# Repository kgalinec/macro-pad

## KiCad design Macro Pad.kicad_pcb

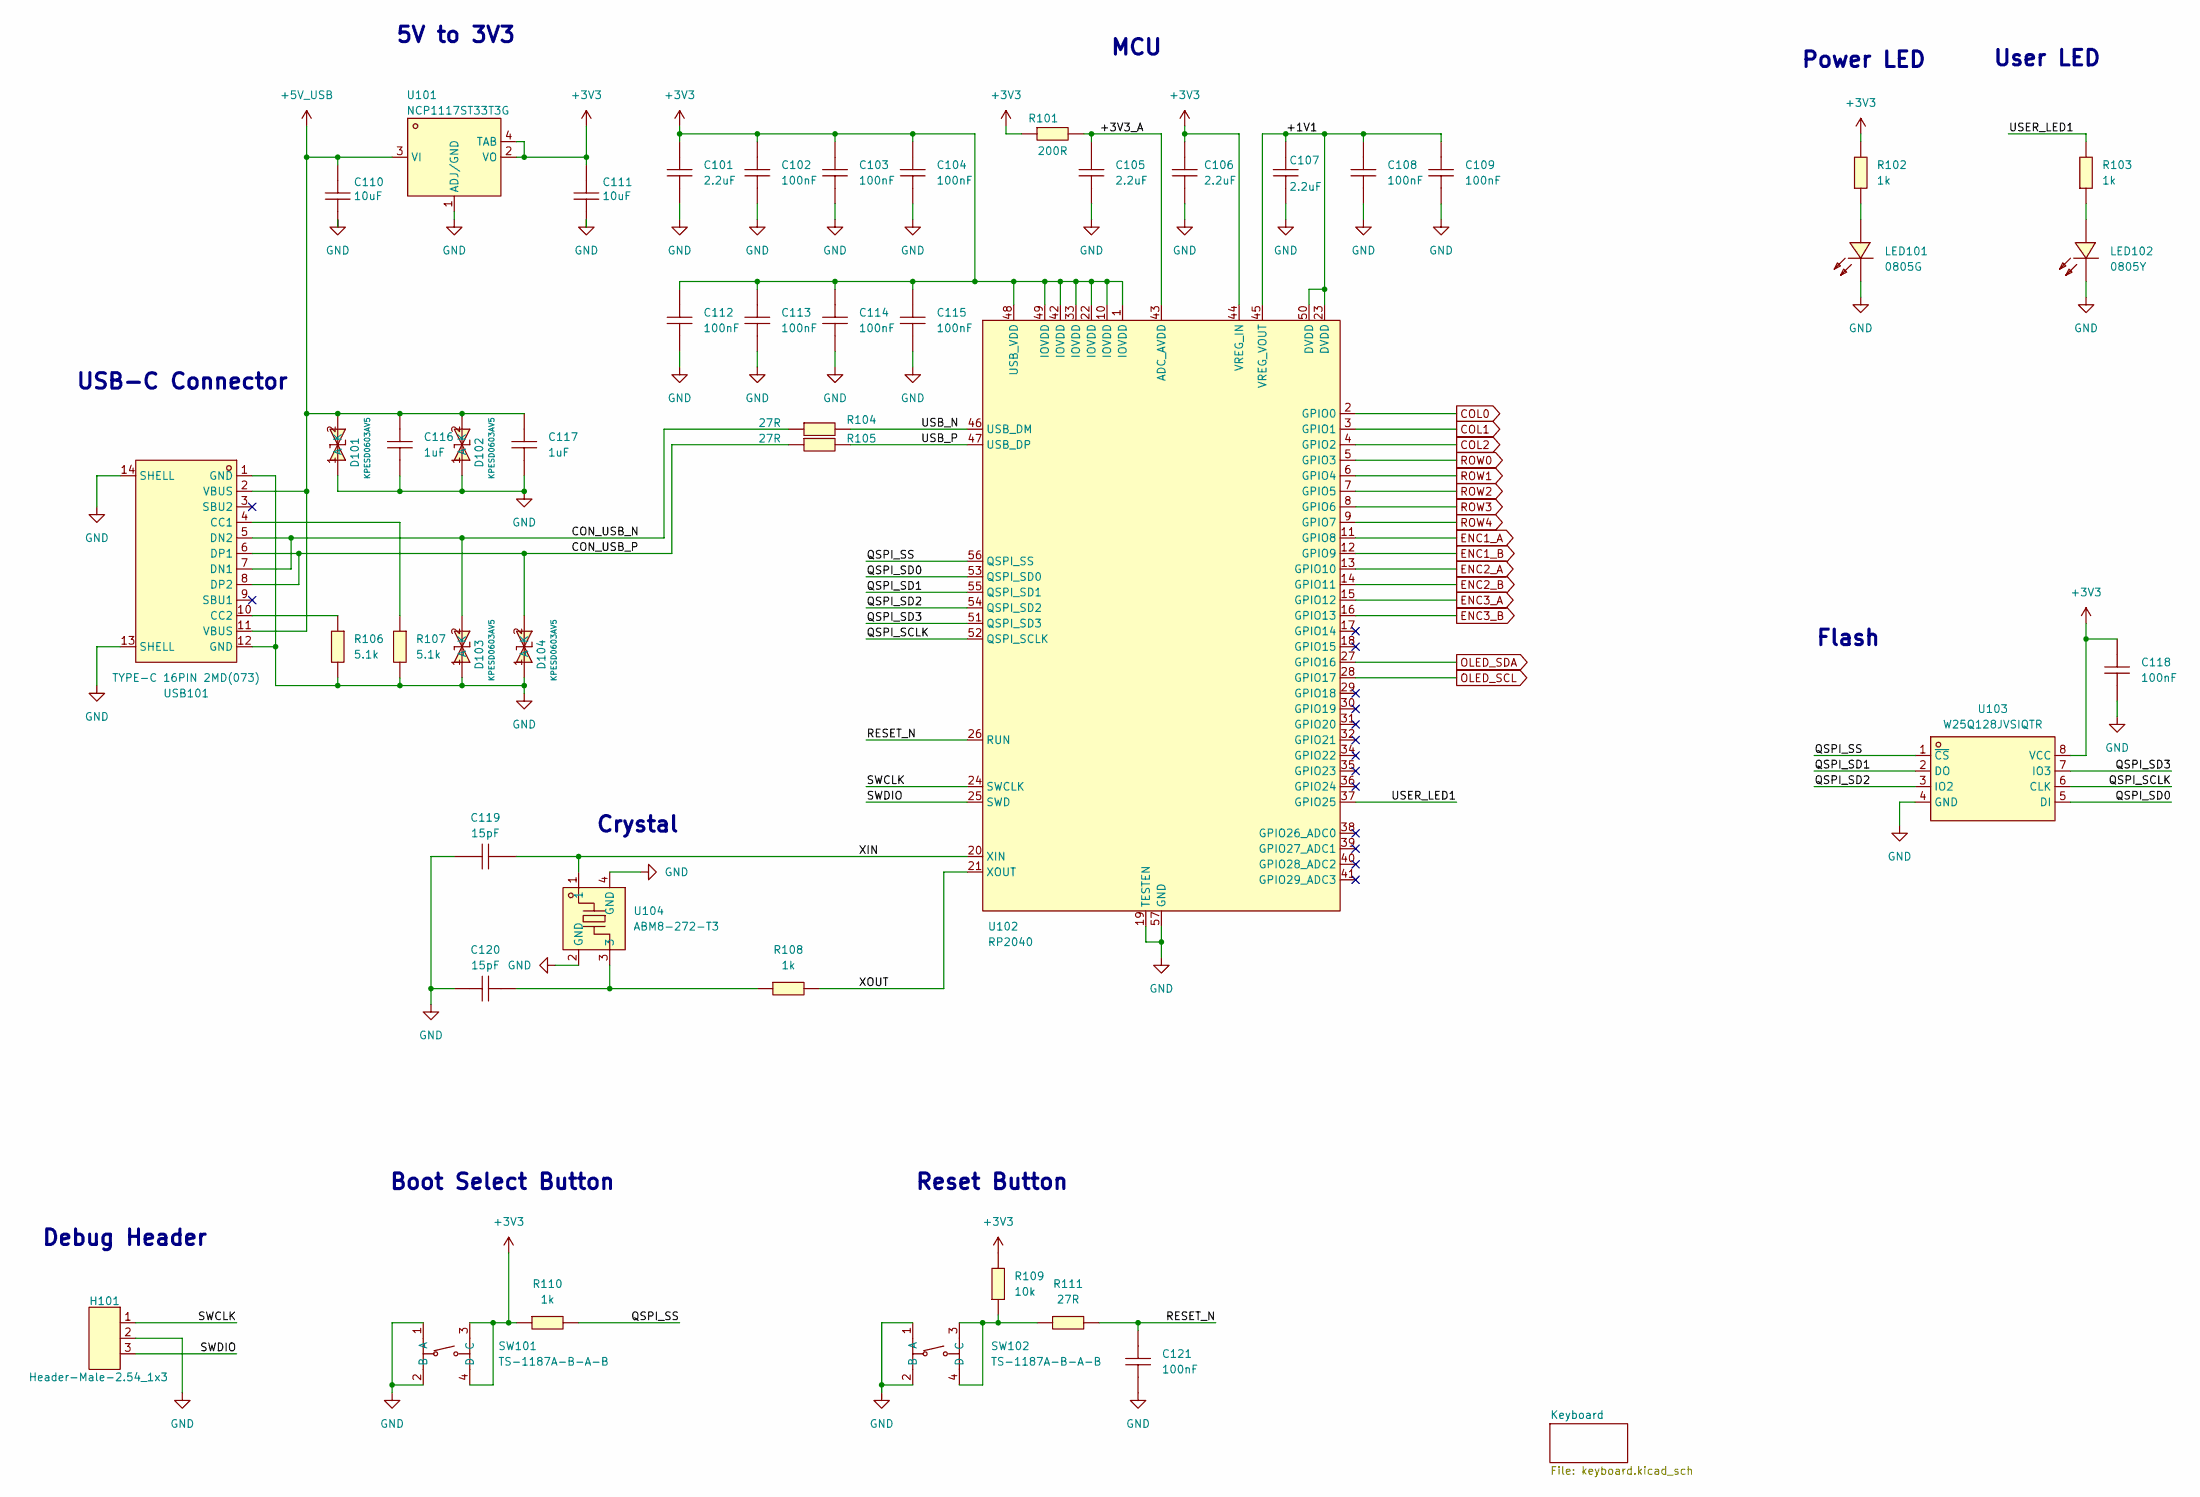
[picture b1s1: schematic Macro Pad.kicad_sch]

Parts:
C101, C105, C106, C107: 2.2uF; C0603; LCSC Part C23630
C102, C103, C104, C108, C109, C112, C113, C114, C115, C118, C121: 100nF; C0603; LCSC Part C1591
C110, C111: 10uF; C0603; LCSC Part C1691
C116, C117: 1uF; C0603; LCSC Part C15849
C119, C120: 15pF; C0603; LCSC Part C1644
D101, D102, D103, D104: KPESD0603AV5; D0603-BI-A; LCSC Part C2944167
H101: Header-Male-2.54_1x3; HDR-TH_3P-P2.54-V-M-1; LCSC Part C49257
LED101: 0805G; LED0805-R-RD; LCSC Part C2297
LED102: 0805Y; LED0805-R-RD; LCSC Part C2296
R101: 200R; R0603; LCSC Part C8218
R102, R103, R108, R110: 1k; R0603; LCSC Part C21190
R104, R105, R111: 27R; R0603; LCSC Part C25190
R106, R107: 5.1k; R0603; LCSC Part C23186
R109: 10k; R0603; LCSC Part C25804
SW101, SW102: TS-1187A-B-A-B; SW-SMD_4P-L5.1-W5.1-P3.70-LS6.5-TL_H1.5; LCSC Part C318884
U101: NCP1117ST33T3G; SOT-223-3_L6.5-W3.4-P2.30-LS7.0-BR; LCSC Part C26537
U102: RP2040; LQFN-56_L7.0-W7.0-P0.4-EP; LCSC Part C2040
U103: W25Q128JVSIQTR; SOIC-8_L5.3-W5.3-P1.27-LS8.0-BL; LCSC Part C97521
U104: ABM8-272-T3; CRYSTAL-SMD_4P-L3.2-W2.5-BL; LCSC Part C20625731
USB101: TYPE-C 16PIN 2MD(073); USB-C-SMD_TYPE-C-6PIN-2MD-073; LCSC Part C2765186

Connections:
+3V3: C101.2, C102.2, C103.2, C104.2, C106.2, C111.2, C112.2, C113.2, C114.2, C115.2, C118.2, R101.1, R102.2, R109.2, R110.1, SW101.3 (C), SW101.4 (D), U101.2 (VO), U101.4 (TAB), U102.1 (IOVDD), U102.10 (IOVDD), U102.22 (IOVDD), U102.33 (IOVDD), U102.42 (IOVDD), U102.44 (VREG_IN), U102.48 (USB_VDD), U102.49 (IOVDD), U103.8 (VCC); also elsewhere on the board
+5V_USB: C110.2, C116.2, C117.2, D101.2 (A), D102.2 (A), U101.3 (VI), USB101.2 (VBUS), USB101.11 (VBUS)
/+1V1: C107.2, C108.2, C109.2, U102.23 (DVDD), U102.45 (VREG_VOUT), U102.50 (DVDD)
/+3V3_A: C105.2, R101.2, U102.43 (ADC_AVDD)
/CON_USB_N: D103.2 (A), R104.1, USB101.5 (DN2), USB101.7 (DN1)
/CON_USB_P: D104.2 (A), R105.1, USB101.6 (DP1), USB101.8 (DP2)
/QSPI_SCLK: U102.52 (QSPI_SCLK), U103.6 (CLK)
/QSPI_SD0: U102.53 (QSPI_SD0), U103.5 (DI)
/QSPI_SD1: U102.55 (QSPI_SD1), U103.2 (DO)
/QSPI_SD2: U102.54 (QSPI_SD2), U103.3 (IO2)
/QSPI_SD3: U102.51 (QSPI_SD3), U103.7 (IO3)
/QSPI_SS: R110.2, U102.56 (QSPI_SS), U103.1 (~CS)
/RESET_N: C121.2, R111.2, U102.26 (RUN)
/SWCLK: H101.1, U102.24 (SWCLK)
/SWDIO: H101.3, U102.25 (SWD)
/USB_N: R104.2, U102.46 (USB_DM)
/USB_P: R105.2, U102.47 (USB_DP)
/USER_LED1: R103.2, U102.37 (GPIO25)
/XIN: C119.1, U102.20 (XIN), U104.1
/XOUT: R108.2, U102.21 (XOUT)
COL0: U102.2 (GPIO0); also elsewhere on the board
COL1: U102.3 (GPIO1); also elsewhere on the board
COL2: U102.4 (GPIO2); also elsewhere on the board
ENC1_A: U102.11 (GPIO8); also elsewhere on the board
ENC1_B: U102.12 (GPIO9); also elsewhere on the board
ENC2_A: U102.13 (GPIO10); also elsewhere on the board
ENC2_B: U102.14 (GPIO11); also elsewhere on the board
ENC3_A: U102.15 (GPIO12); also elsewhere on the board
ENC3_B: U102.16 (GPIO13); also elsewhere on the board
GND: C101.1, C102.1, C103.1, C104.1, C105.1, C106.1, C107.1, C108.1, C109.1, C110.1, C111.1, C112.1, C113.1, C114.1, C115.1, C116.1, C117.1, C118.1, C119.2, C120.2, C121.1, D101.1 (K), D102.1 (K), D103.1 (K), D104.1 (K), H101.2, LED101.2 (K), LED102.2 (K), R106.2, R107.2, SW101.1 (A), SW101.2 (B), SW102.1 (A), SW102.2 (B), U101.1 (ADJ/GND), U102.19 (TESTEN), U102.57 (GND), U103.4 (GND), U104.2 (GND), U104.4 (GND), USB101.1 (GND), USB101.12 (GND), USB101.13 (SHELL), USB101.14 (SHELL); also elsewhere on the board
unnamed: C120.1, R108.1, U104.3
unnamed: LED101.1 (A), R102.1
unnamed: LED102.1 (A), R103.1
unnamed: R109.1, R111.1, SW102.3 (C), SW102.4 (D)
unnamed: R107.1, USB101.4 (CC1)
unnamed: R106.1, USB101.10 (CC2)
OLED_SCL: U102.28 (GPIO17); also elsewhere on the board
OLED_SDA: U102.27 (GPIO16); also elsewhere on the board
ROW0: U102.5 (GPIO3); also elsewhere on the board
ROW1: U102.6 (GPIO4); also elsewhere on the board
ROW2: U102.7 (GPIO5); also elsewhere on the board
ROW3: U102.8 (GPIO6); also elsewhere on the board
ROW4: U102.9 (GPIO7); also elsewhere on the board

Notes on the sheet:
MCU
Crystal
Power LED
Boot Select Button
Debug Header
Flash
Reset Button
5V to 3V3
USB-C Connector
User LED

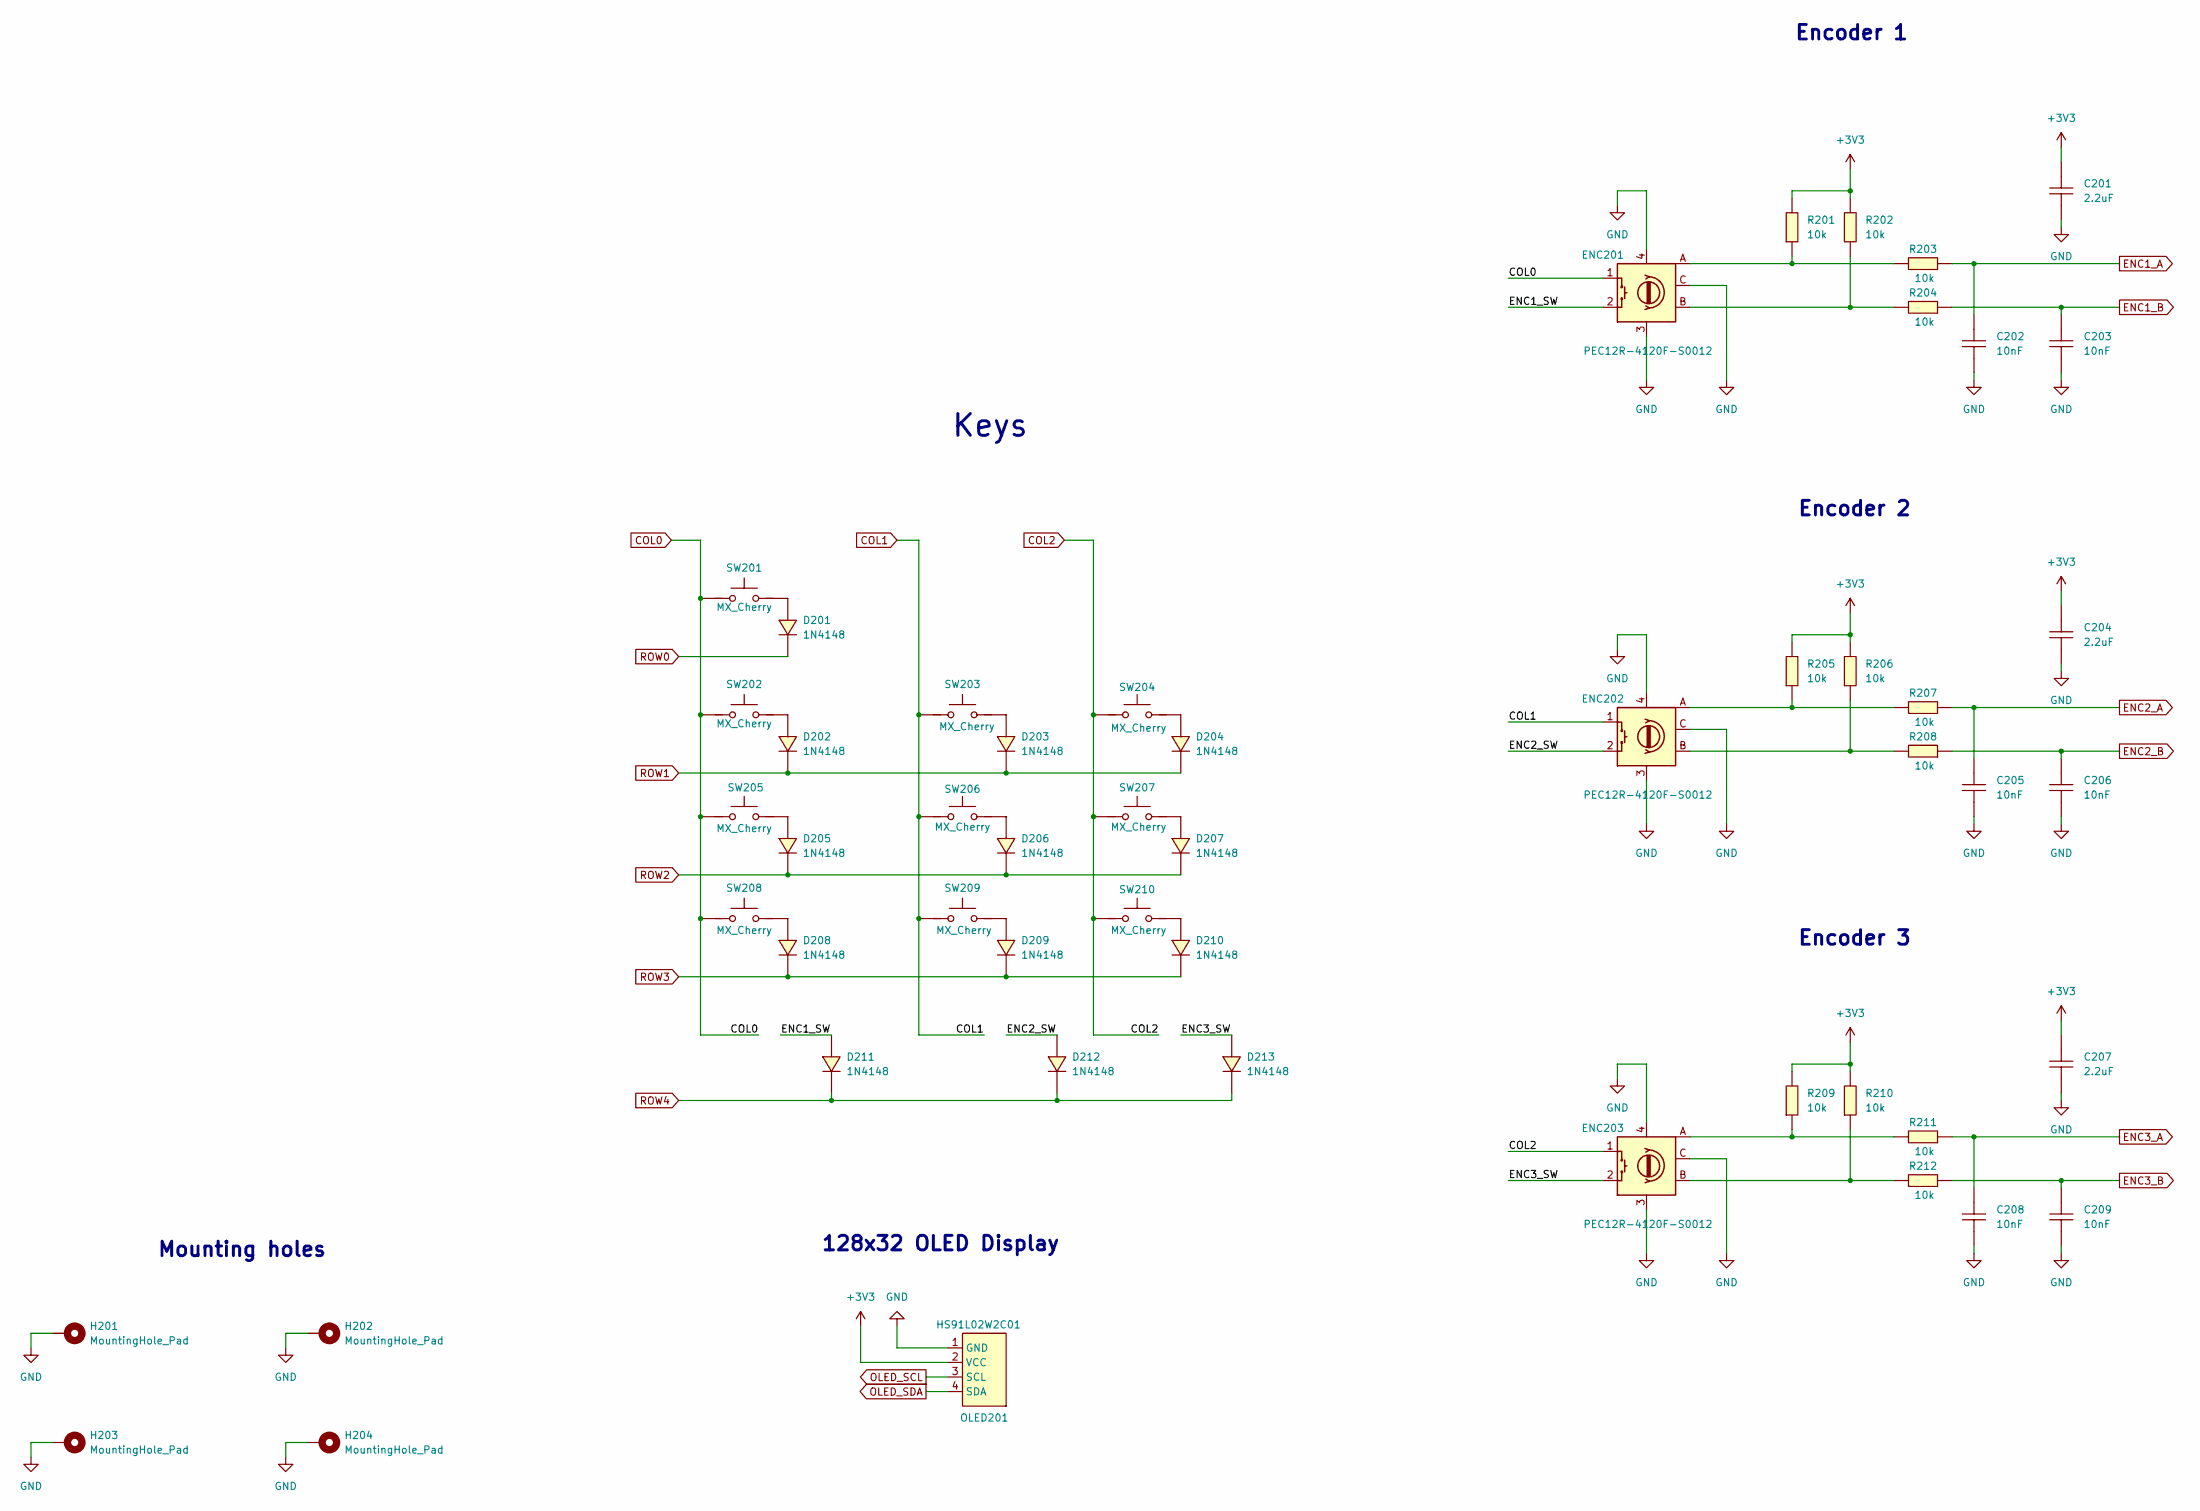
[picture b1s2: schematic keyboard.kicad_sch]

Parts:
C201, C204, C207: 2.2uF; C0603; LCSC Part C23630
C202, C203, C205, C206, C208, C209: 10nF; C0603; LCSC Part C1589
D201, D202, D203, D204, D205, D206, D207, D208, D209, D210, D211, D212, D213: 1N4148; SOD-323_L1.8-W1.3-LS2.5-RD; LCSC Part C2128
ENC201, ENC202, ENC203: PEC12R-4120F-S0012; SW-TH_PEC12R-4120F-S0012; LCSC Part C143801
H201, H202, H203, H204: MountingHole_Pad; MountingHole_3.2mm_M3_ISO14580_Pad
OLED201: HS91L02W2C01; OLED-TH_L38.0-W12.0_HS91L02W2C01; LCSC Part C5248081
R201, R202, R203, R204, R205, R206, R207, R208, R209, R210, R211, R212: 10k; R0603; LCSC Part C25804
SW201, SW202, SW203, SW204, SW206, SW207, SW208, SW209, SW210: MX_Cherry; KEY-TH_CPG151101D21X; LCSC Part C400235
SW205: MX_Cherry; KEY-TH_CPG151101D21X

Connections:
+3V3: C201.2, C204.2, C207.2, OLED201.2 (VCC), R201.2, R202.2, R205.2, R206.2, R209.2, R210.2; also elsewhere on the board
/Keyboard/ENC1_SW: D211.2 (A), ENC201.2
/Keyboard/ENC2_SW: D212.2 (A), ENC202.2
/Keyboard/ENC3_SW: D213.2 (A), ENC203.2
COL0: ENC201.1, SW201.1, SW202.1, SW205.1, SW208.1; also elsewhere on the board
COL1: ENC202.1, SW203.1, SW206.1, SW209.1; also elsewhere on the board
COL2: ENC203.1, SW204.1, SW207.1, SW210.1; also elsewhere on the board
ENC1_A: C202.2, R203.1; also elsewhere on the board
ENC1_B: C203.2, R204.1; also elsewhere on the board
ENC2_A: C205.2, R207.1; also elsewhere on the board
ENC2_B: C206.2, R208.1; also elsewhere on the board
ENC3_A: C208.2, R211.1; also elsewhere on the board
ENC3_B: C209.2, R212.1; also elsewhere on the board
GND: C201.1, C202.1, C203.1, C204.1, C205.1, C206.1, C207.1, C208.1, C209.1, ENC201.3, ENC201.4, ENC201.C, ENC202.3, ENC202.4, ENC202.C, ENC203.3, ENC203.4, ENC203.C, H201.1, H202.1, H203.1, H204.1, OLED201.1 (GND); also elsewhere on the board
unnamed: D201.2 (A), SW201.2
unnamed: D202.2 (A), SW202.2
unnamed: D203.2 (A), SW203.2
unnamed: D204.2 (A), SW204.2
unnamed: D205.2 (A), SW205.2
unnamed: D206.2 (A), SW206.2
unnamed: D207.2 (A), SW207.2
unnamed: D208.2 (A), SW208.2
unnamed: D209.2 (A), SW209.2
unnamed: D210.2 (A), SW210.2
unnamed: ENC201.A, R201.1, R203.2
unnamed: ENC201.B, R202.1, R204.2
unnamed: ENC202.A, R205.1, R207.2
unnamed: ENC202.B, R206.1, R208.2
unnamed: ENC203.A, R209.1, R211.2
unnamed: ENC203.B, R210.1, R212.2
OLED_SCL: OLED201.3 (SCL); also elsewhere on the board
OLED_SDA: OLED201.4 (SDA); also elsewhere on the board
ROW0: D201.1 (K); also elsewhere on the board
ROW1: D202.1 (K), D203.1 (K), D204.1 (K); also elsewhere on the board
ROW2: D205.1 (K), D206.1 (K), D207.1 (K); also elsewhere on the board
ROW3: D208.1 (K), D209.1 (K), D210.1 (K); also elsewhere on the board
ROW4: D211.1 (K), D212.1 (K), D213.1 (K); also elsewhere on the board

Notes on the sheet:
Encoder 2
Encoder 3
Encoder 1
Mounting holes
128x32 OLED Display
Keys

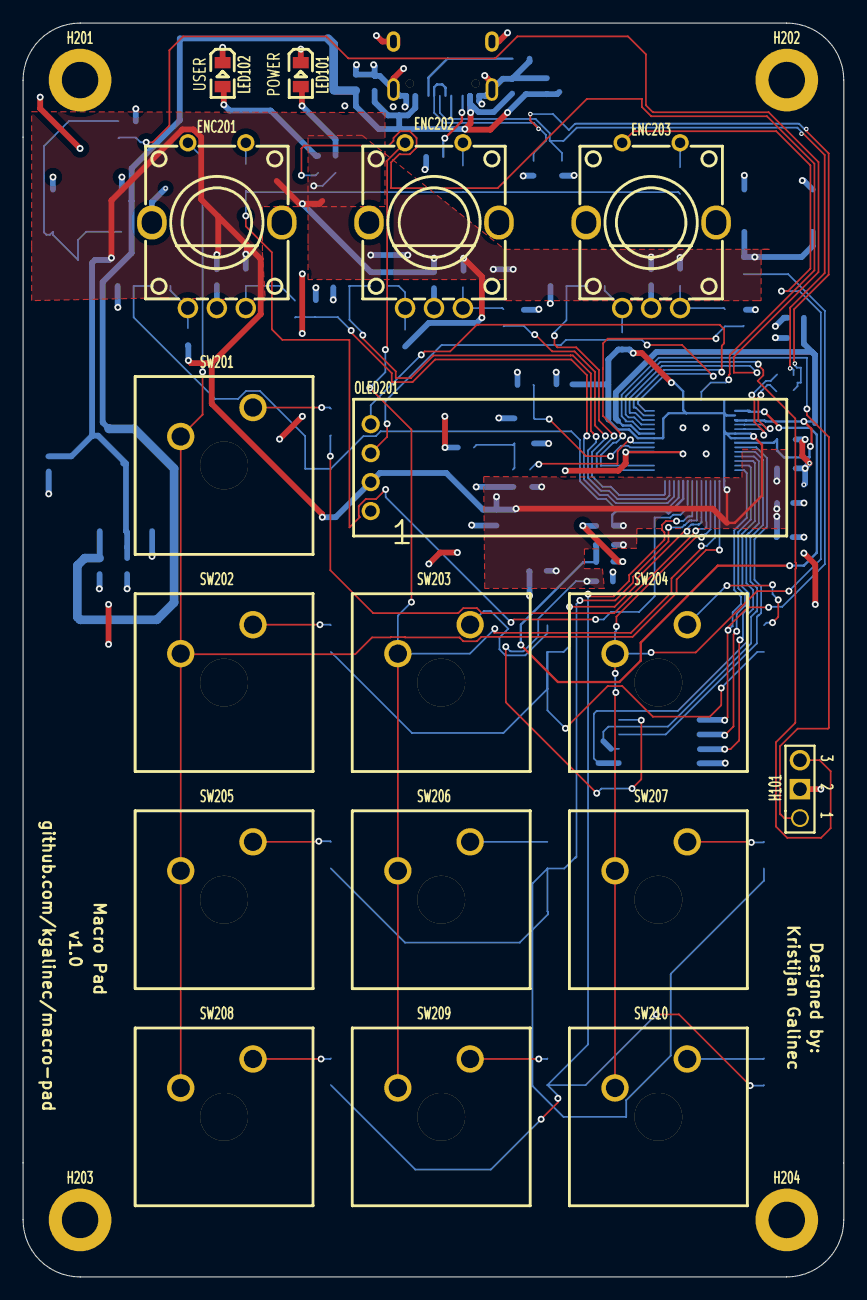
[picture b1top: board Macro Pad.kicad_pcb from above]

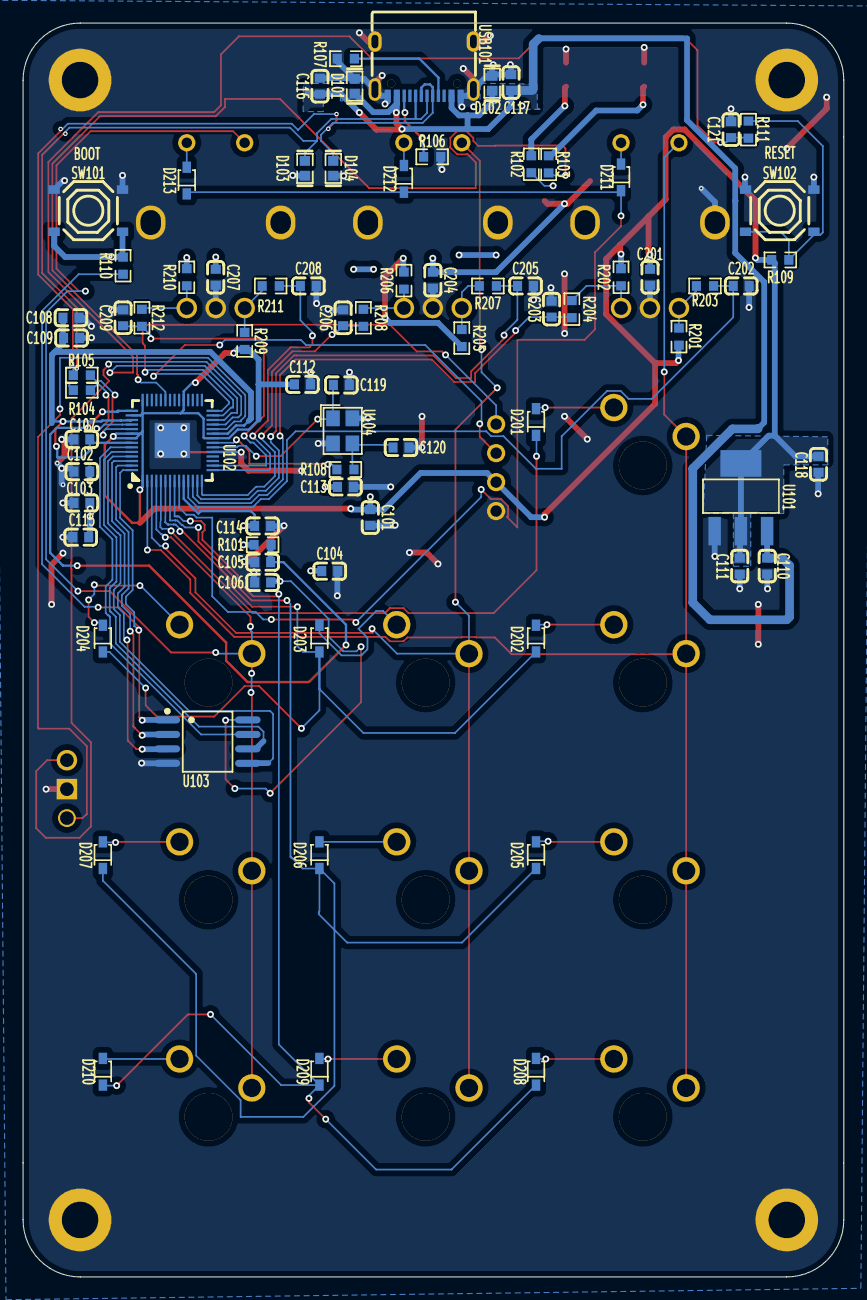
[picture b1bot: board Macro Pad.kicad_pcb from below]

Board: 2 copper layers, 72.0 x 110.0 mm, 98 parts (77 on the bottom side), 62 nets.
